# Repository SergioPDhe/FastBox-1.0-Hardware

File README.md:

# FastBox 1.0 Hardware
 Hardware design for FastBox. 
 
 Split into two designs: Standalone and Modular.

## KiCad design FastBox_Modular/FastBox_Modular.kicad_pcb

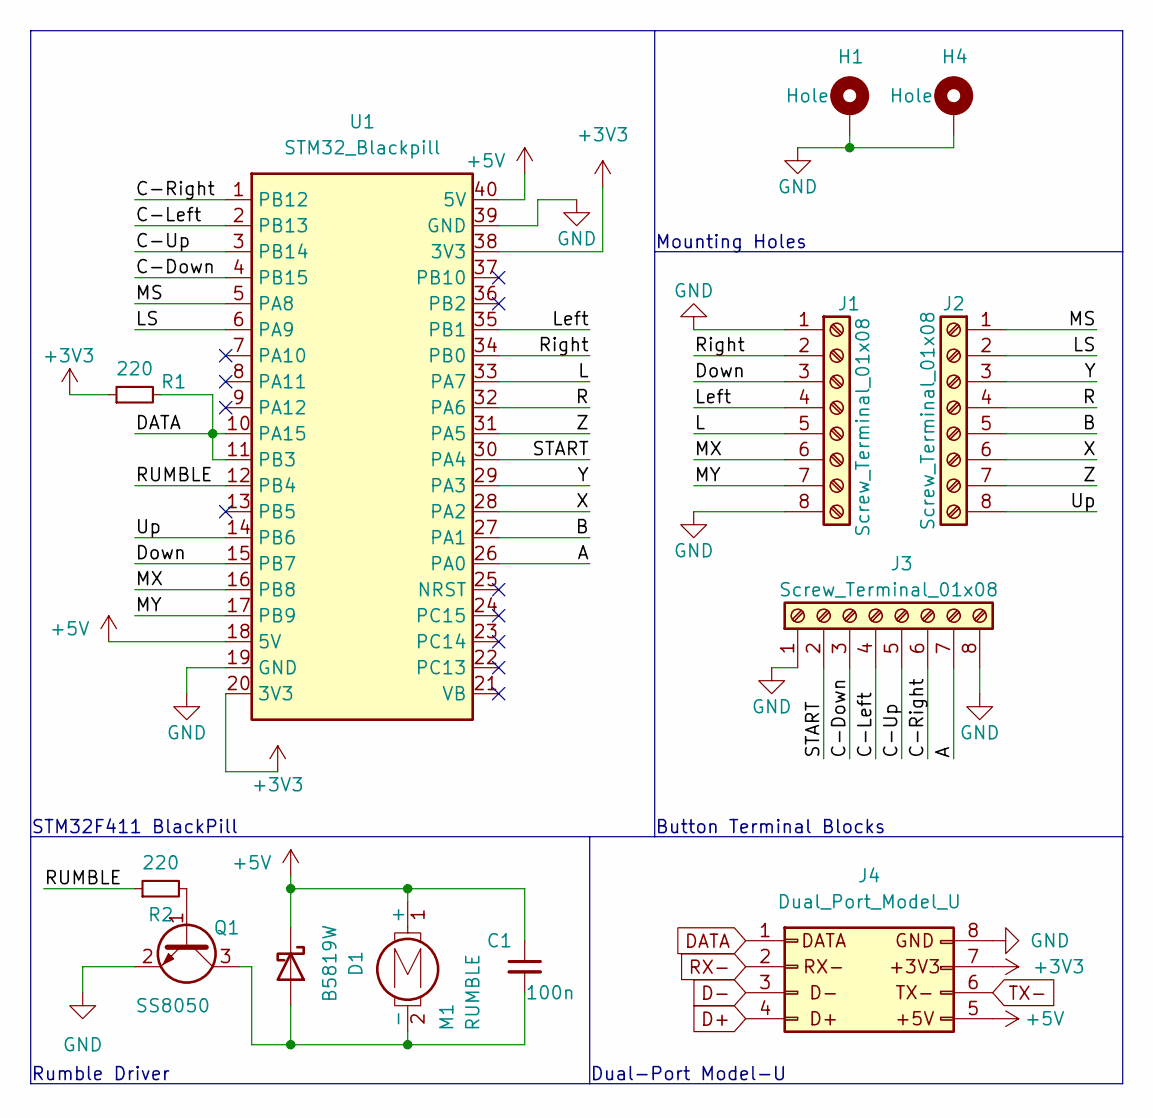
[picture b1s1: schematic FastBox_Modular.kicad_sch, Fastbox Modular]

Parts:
C1: 100n; C_0402_1005Metric
D1: B5819W; D_SOD-123
H1, H4: Hole; MountingHole_4.3mm_M4_Pad
J1, J2, J3: Screw_Terminal_01x08; TerminalBlock_Phoenix_MPT-0,5-8-2.54_1x08_P2.54mm_Horizontal
J4: Dual_Port_Model_U
M1: RUMBLE; TerminalBlock_Phoenix_MPT-0,5-2-2.54_1x02_P2.54mm_Horizontal
Q1: SS8050; SOT-23
R1, R2: 220; R_0603_1608Metric
U1: STM32_Blackpill

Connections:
+3V3: J4.7, R1.1, U1.20 (3V3), U1.38 (3V3)
+5V: C1.1, D1.1 (K), J4.5, M1.1 (+), U1.18 (5V), U1.40 (5V)
/A: J3.7, U1.26 (PA0)
/B: J2.5, U1.27 (PA1)
/C-Down: J3.3, U1.4 (PB15)
/C-Left: J3.4, U1.2 (PB13)
/C-Right: J3.6, U1.1 (PB12)
/C-Up: J3.5, U1.3 (PB14)
/Down: J1.3, U1.15 (PB7)
/L: J1.5, U1.33 (PA7)
/LS: J2.2, U1.6 (PA9)
/Left: J1.4, U1.35 (PB1)
/MS: J2.1, U1.5 (PA8)
/MX: J1.6, U1.16 (PB8)
/MY: J1.7, U1.17 (PB9)
/R: J2.4, U1.32 (PA6)
/RUMBLE: R2.1, U1.12 (PB4)
/Right: J1.2, U1.34 (PB0)
/START: J3.2, U1.30 (PA4)
/Up: J2.8, U1.14 (PB6)
/X: J2.6, U1.28 (PA2)
/Y: J2.3, U1.29 (PA3)
/Z: J2.7, U1.31 (PA5)
D+: J4.4
D-: J4.3
DATA: J4.1, R1.2, U1.10 (PA15), U1.11 (PB3)
GND: H1.1, H4.1, J1.1, J1.8, J3.1, J3.8, J4.8, Q1.2 (E), U1.19 (GND), U1.39 (GND)
unnamed: C1.2, D1.2 (A), M1.2 (-), Q1.3 (C)
unnamed: Q1.1 (B), R2.2
RX-: J4.2
TX-: J4.6

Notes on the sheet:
Mounting Holes
STM32F411 BlackPill
Button Terminal Blocks
Rumble Driver
Dual-Port Model-U

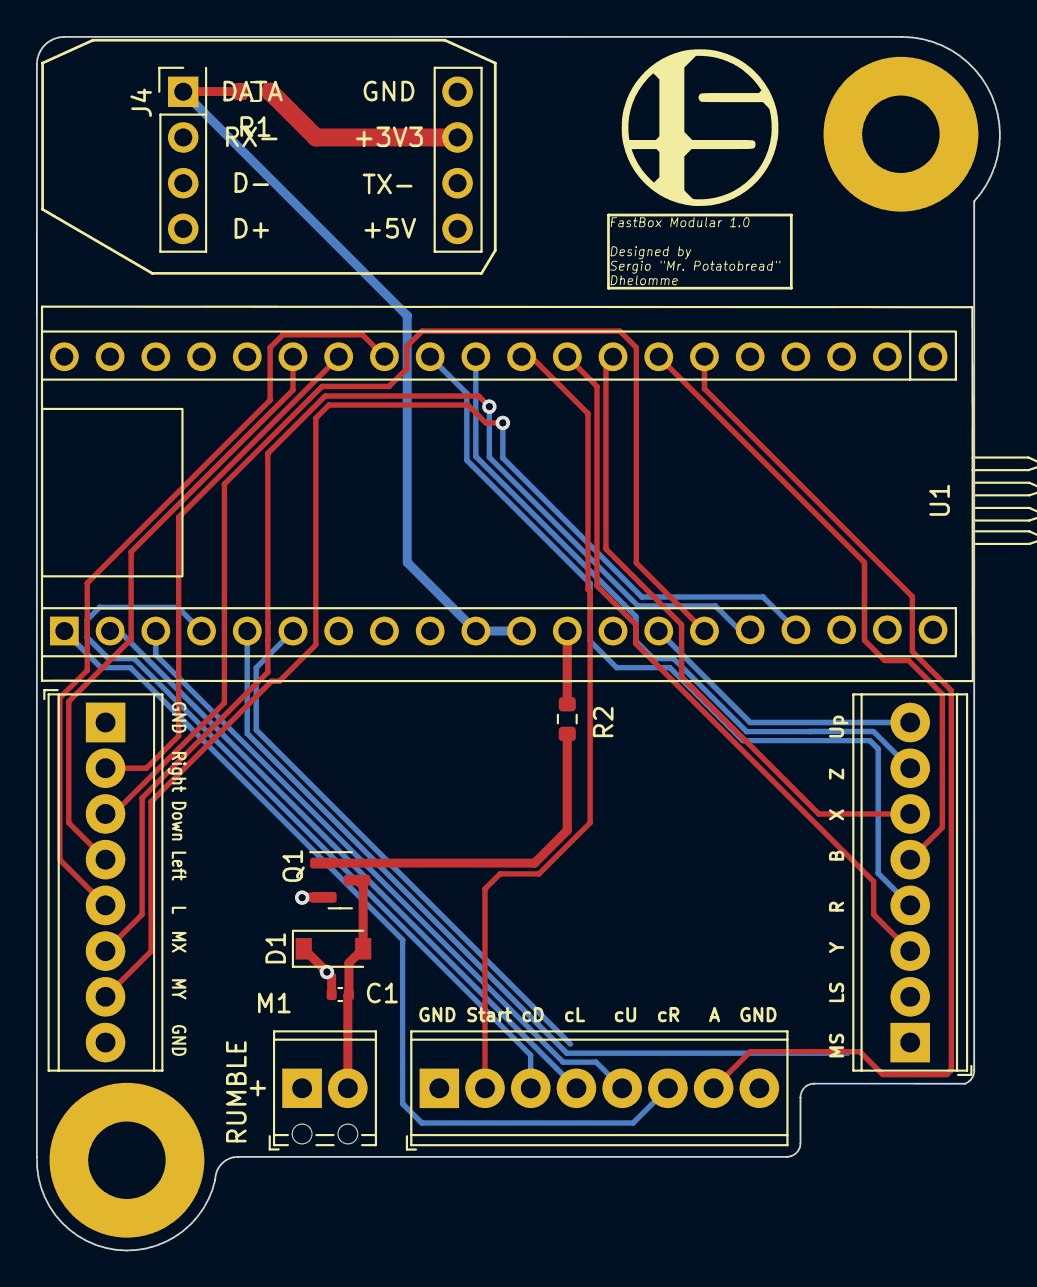
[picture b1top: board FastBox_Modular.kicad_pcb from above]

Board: 4 copper layers, 53.5 x 67.4 mm, 13 parts (0 on the bottom side), 27 nets.

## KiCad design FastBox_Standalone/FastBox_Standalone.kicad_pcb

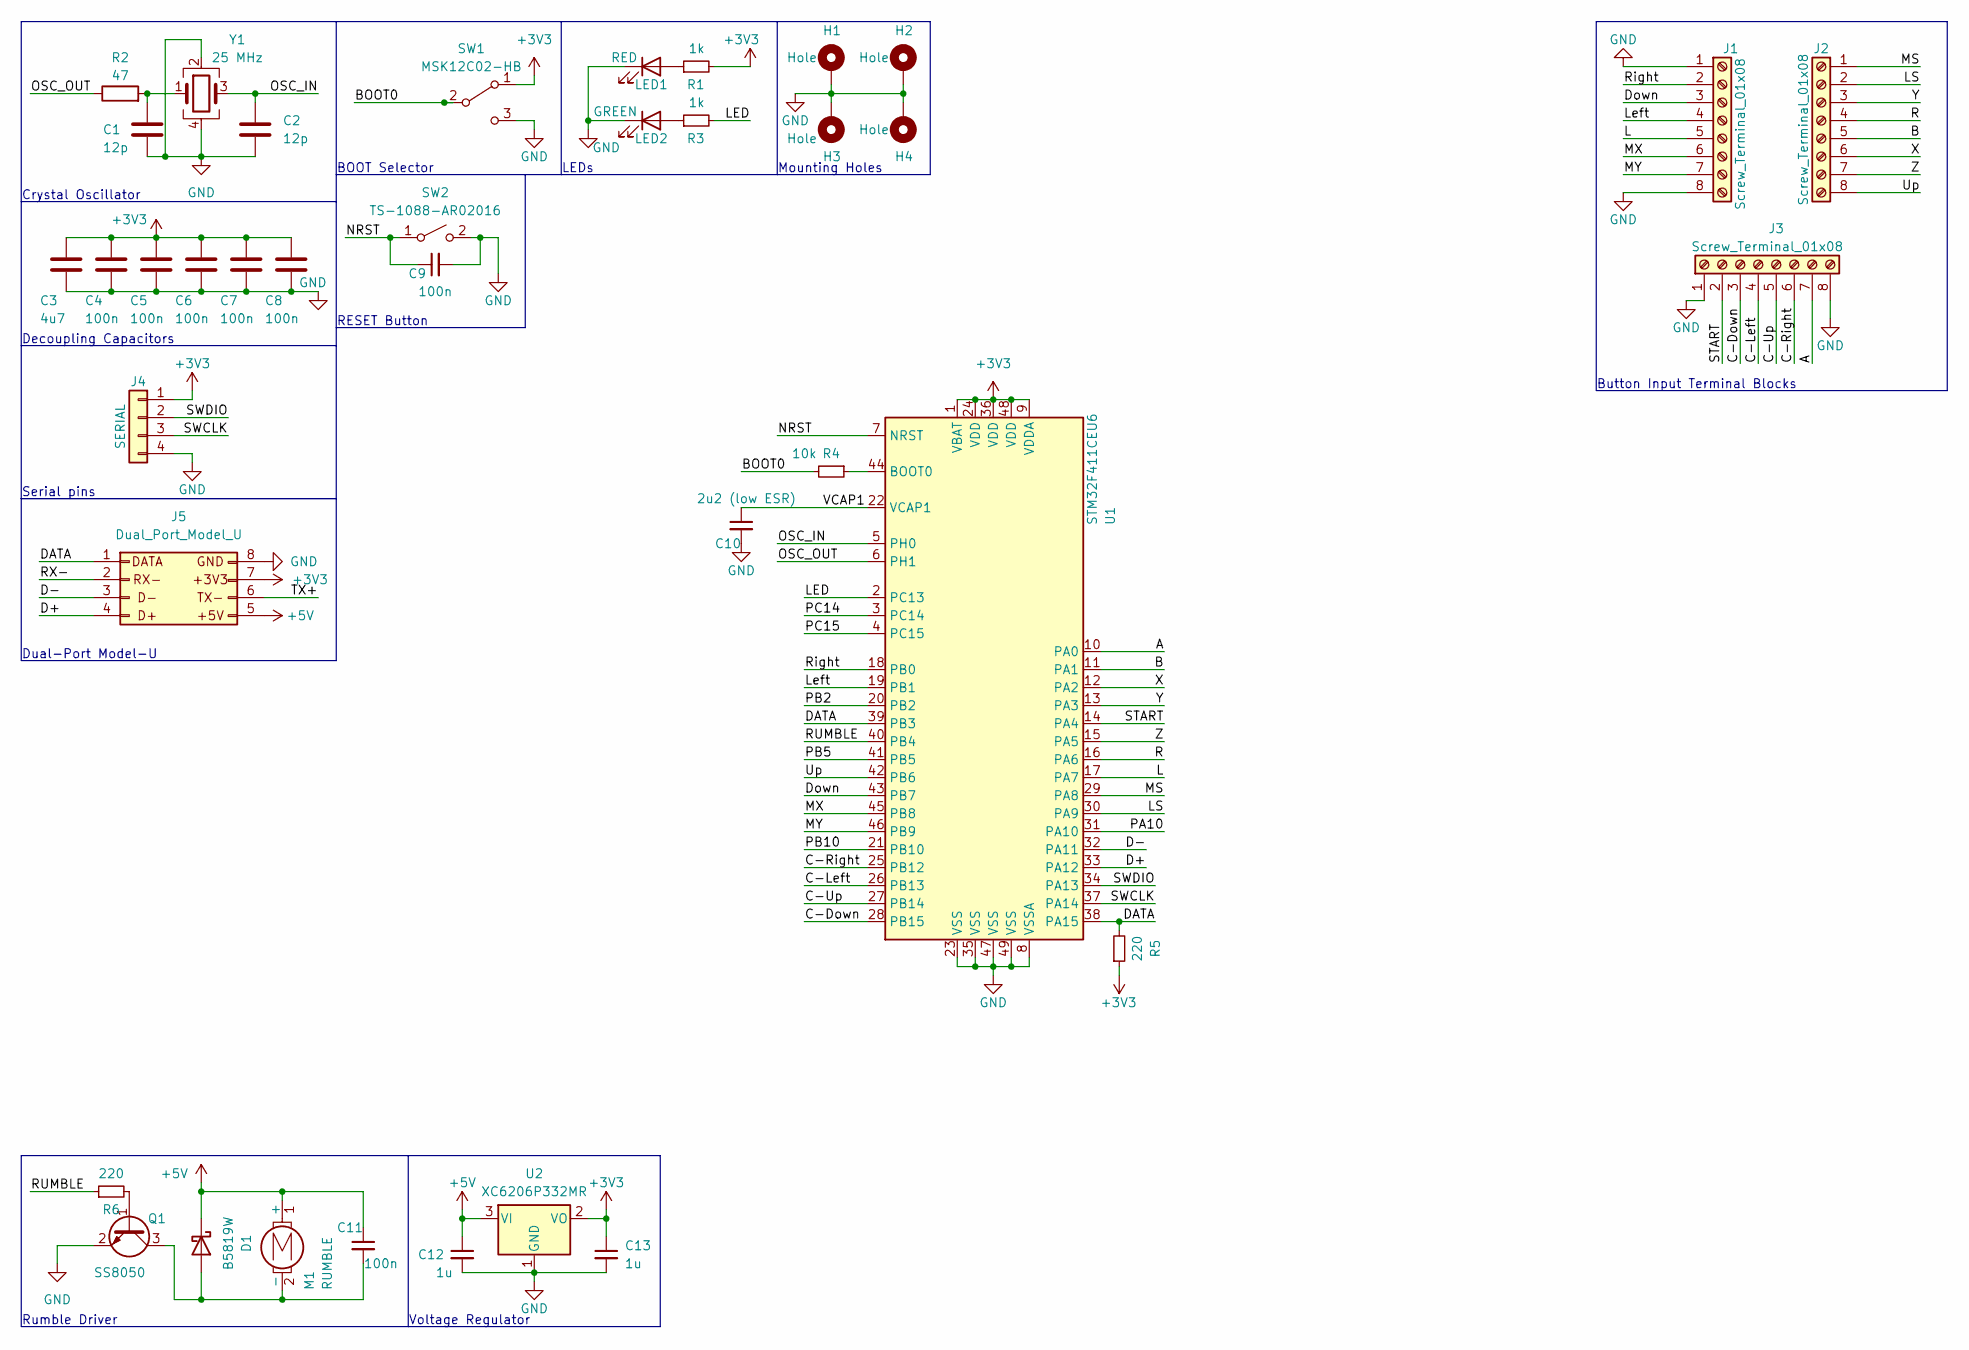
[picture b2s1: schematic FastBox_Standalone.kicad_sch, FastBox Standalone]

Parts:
C1, C2: 12p; C_0402_1005Metric_Pad0.74x0.62mm_HandSolder; LCSC part # C1547
C3: 4u7; C_0805_2012Metric; LCSC part # C1779
C4, C5, C6, C7, C8: 100n; C_0402_1005Metric_Pad0.74x0.62mm_HandSolder; LCSC part # C307331
C9, C11: 100n; C_0402_1005Metric_Pad0.74x0.62mm_HandSolder
C10: 2u2 (low ESR); C_0603_1608Metric; LCSC part # C23630
C12, C13: 1u; C_0603_1608Metric
D1: B5819W; D_SOD-123
H1, H2, H3, H4: Hole; MountingHole_4.3mm_M4_Pad
J1, J2, J3: Screw_Terminal_01x08; TerminalBlock_Phoenix_MPT-0,5-8-2.54_1x08_P2.54mm_Horizontal
J4: SERIAL; PinHeader_1x04_P2.54mm_Horizontal
J5: Dual_Port_Model_U
LED1: RED; LED_0603_1608Metric
LED2: GREEN; LED_0603_1608Metric
M1: RUMBLE; TerminalBlock_Phoenix_MPT-0,5-2-2.54_1x02_P2.54mm_Horizontal
Q1: SS8050; SOT-23
R1, R3: 1k; R_0603_1608Metric
R2: 47; R_0402_1005Metric
R4: 10k; R_0402_1005Metric
R5, R6: 220; R_0603_1608Metric
SW1: MSK12C02-HB; SW_SPDT_PCM12
SW2: TS-1088-AR02016; SW_Push_SPST_NO_Alps_SKRK
U1: STM32F411CEU6; QFN-48-1EP_7x7mm_P0.5mm_EP5.6x5.6mm
U2: XC6206P332MR; SOT-23
Y1: 25 MHz; Crystal_SMD_3225-4Pin_3.2x2.5mm

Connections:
+3V3: C3.1, C4.1, C5.1, C6.1, C7.1, C8.1, C13.1, J4.1, J5.7, R1.2, R5.1, SW1.1 (A), U1.1 (VBAT), U1.9 (VDDA), U1.24 (VDD), U1.36 (VDD), U1.48 (VDD), U2.2 (VO)
+5V: C11.1, C12.1, D1.1 (K), J5.5, M1.1 (+), U2.3 (VI)
/A: J3.7, U1.10 (PA0)
/B: J2.5, U1.11 (PA1)
/BOOT0: R4.2, SW1.2 (B)
/C-Down: J3.3, U1.28 (PB15)
/C-Left: J3.4, U1.26 (PB13)
/C-Right: J3.6, U1.25 (PB12)
/C-Up: J3.5, U1.27 (PB14)
/D+: J5.4, U1.33 (PA12)
/D-: J5.3, U1.32 (PA11)
/DATA: J5.1, R5.2, U1.38 (PA15), U1.39 (PB3)
/Down: J1.3, U1.43 (PB7)
/L: J1.5, U1.17 (PA7)
/LED: R3.2, U1.2 (PC13)
/LS: J2.2, U1.30 (PA9)
/Left: J1.4, U1.19 (PB1)
/MS: J2.1, U1.29 (PA8)
/MX: J1.6, U1.45 (PB8)
/MY: J1.7, U1.46 (PB9)
/NRST: C9.1, SW2.1 (A), U1.7 (NRST)
/OSC_IN: C2.1, U1.5 (PH0), Y1.3
/OSC_OUT: R2.1, U1.6 (PH1)
/PA10: U1.31 (PA10)
/PB2: U1.20 (PB2)
/PB5: U1.41 (PB5)
/PB10: U1.21 (PB10)
/PC14: U1.3 (PC14)
/PC15: U1.4 (PC15)
/R: J2.4, U1.16 (PA6)
/RUMBLE: R6.1, U1.40 (PB4)
/RX-: J5.2
/Right: J1.2, U1.18 (PB0)
/START: J3.2, U1.14 (PA4)
/SWCLK: J4.3, U1.37 (PA14)
/SWDIO: J4.2, U1.34 (PA13)
/TX+: J5.6
/Up: J2.8, U1.42 (PB6)
/VCAP1: C10.1, U1.22 (VCAP1)
/X: J2.6, U1.12 (PA2)
/Y: J2.3, U1.13 (PA3)
/Z: J2.7, U1.15 (PA5)
GND: C1.2, C2.2, C3.2, C4.2, C5.2, C6.2, C7.2, C8.2, C9.2, C10.2, C12.2, C13.2, H1.1, H2.1, H3.1, H4.1, J1.1, J1.8, J3.1, J3.8, J4.4, J5.8, LED1.1 (K), LED2.1 (K), Q1.2 (E), SW1.3 (C), SW2.2 (B), U1.8 (VSSA), U1.23 (VSS), U1.35 (VSS), U1.47 (VSS), U1.49 (VSS), U2.1 (GND), Y1.2, Y1.4; also elsewhere on the board
unnamed: C1.1, R2.2, Y1.1
unnamed: C11.2, D1.2 (A), M1.2 (-), Q1.3 (C)
unnamed: LED1.2 (A), R1.1
unnamed: LED2.2 (A), R3.1
unnamed: Q1.1 (B), R6.2
unnamed: R4.1, U1.44 (BOOT0)

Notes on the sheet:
LEDs
Decoupling Capacitors
RESET Button
Voltage Regulator
Mounting Holes
Crystal Oscillator
Dual-Port Model-U
BOOT Selector
Button Input Terminal Blocks
Rumble Driver
Serial pins

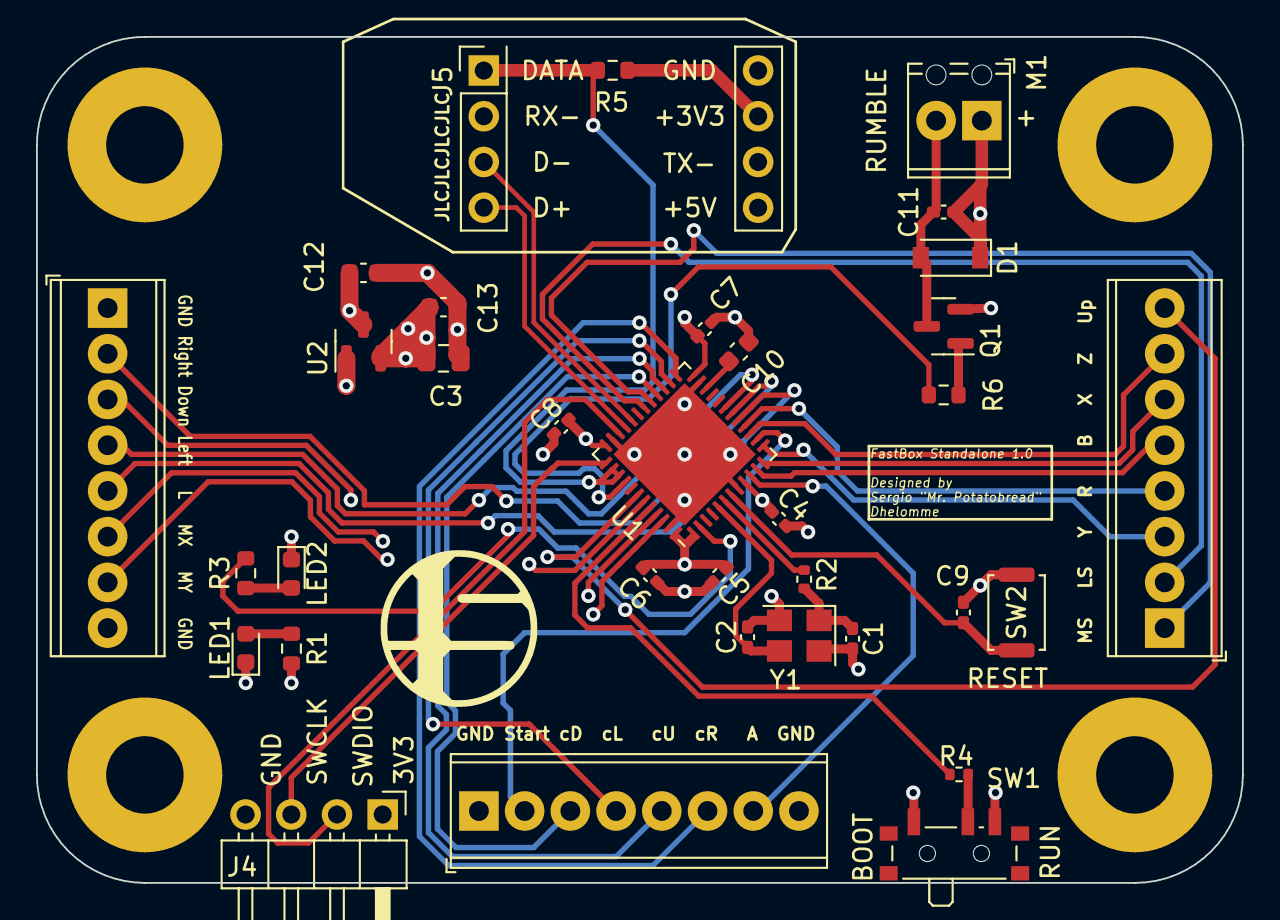
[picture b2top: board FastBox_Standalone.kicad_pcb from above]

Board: 4 copper layers, 67.0 x 47.0 mm, 38 parts (0 on the bottom side), 41 nets.

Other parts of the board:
locked: Hole; MountingHole_4.3mm_M4_Pad
locked#2: Hole; MountingHole_4.3mm_M4_Pad

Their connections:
GND: locked.1, locked#2.1; also elsewhere on the board
